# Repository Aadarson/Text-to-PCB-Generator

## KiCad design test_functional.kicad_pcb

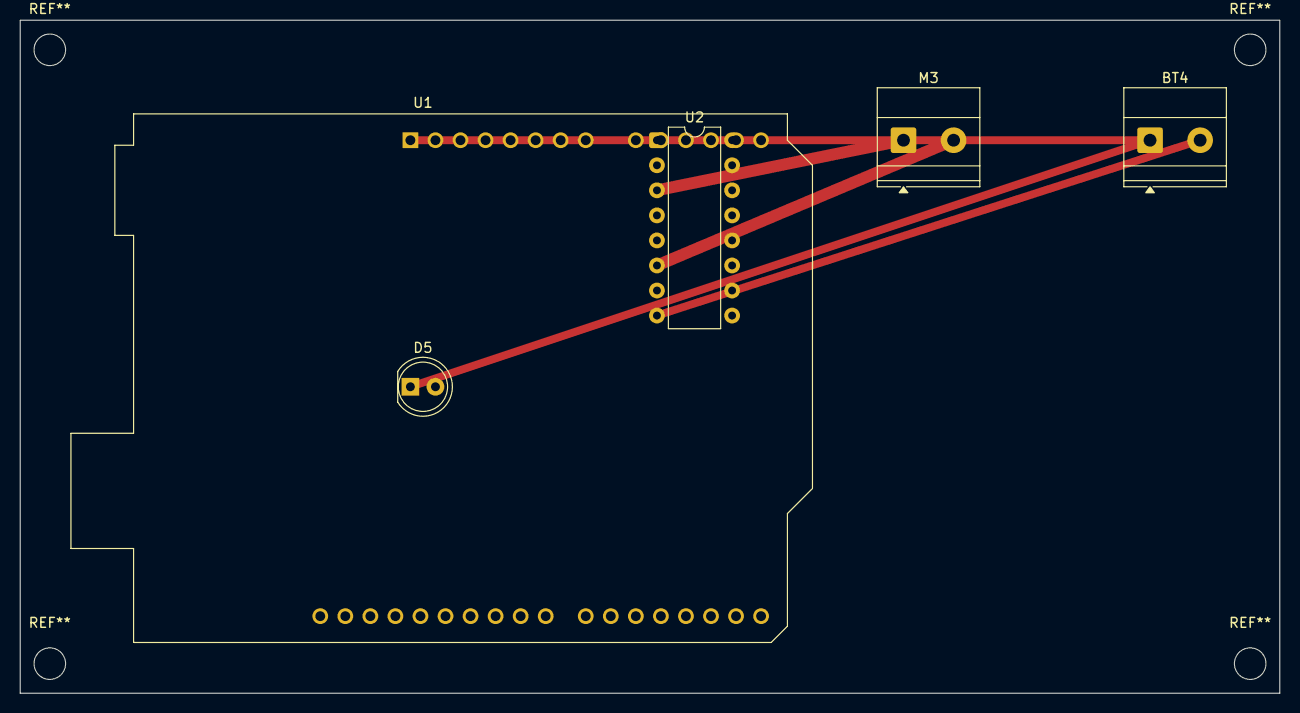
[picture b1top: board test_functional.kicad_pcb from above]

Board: 2 copper layers, 127.7 x 68.2 mm, 5 parts (0 on the bottom side), 4 nets.

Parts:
BT4: Battery; TerminalBlock_Phoenix_MKDS-1,5-2-5.08_1x02_P5.08mm_Horizont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
D5: LED; LED_D5.0mm
M3: Motor; TerminalBlock_Phoenix_MKDS-1,5-2-5.08_1x02_P5.08mm_Horizont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
U1: Arduino; Arduino_UNO_R3
U2: L293D; DIP-16_W7.62mm

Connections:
GND: BT4.1, D5.1, U1.1, U2.1
unnamed: BT4.2, U2.8
unnamed: M3.1, U2.3
unnamed: M3.2, U2.6

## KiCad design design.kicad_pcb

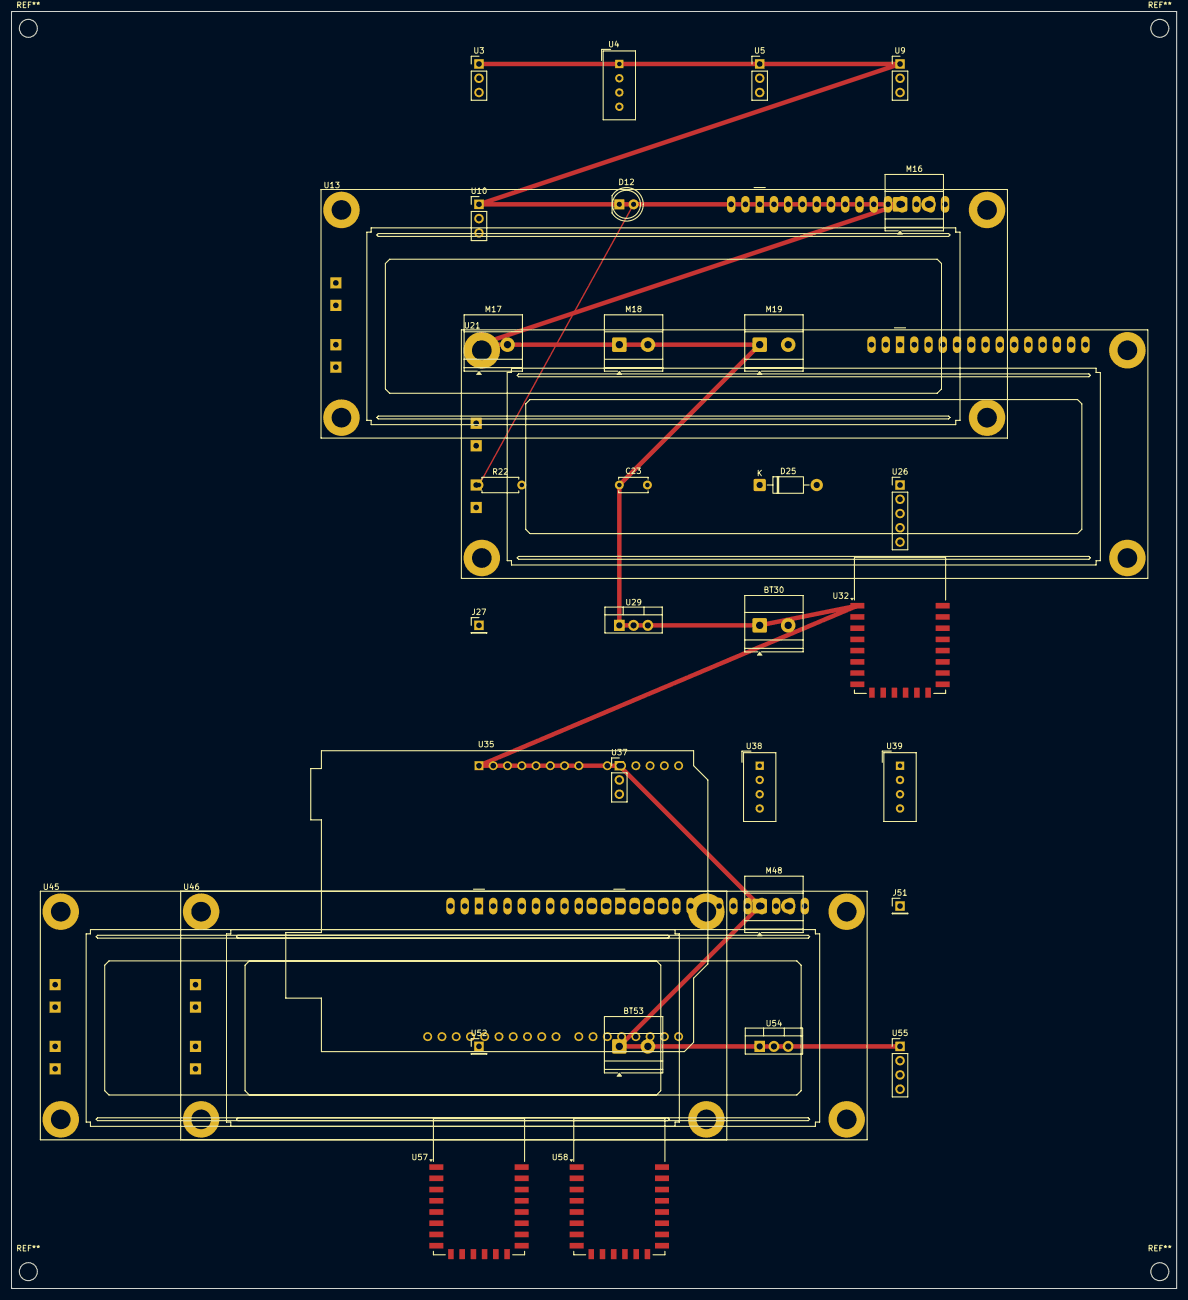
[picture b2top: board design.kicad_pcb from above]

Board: 2 copper layers, 207.6 x 227.5 mm, 34 parts (0 on the bottom side), 2 nets.

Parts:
BT30: Battery holders; TerminalBlock_Phoenix_MKDS-1,5-2-5.08_1x02_P5.08mm_Horizont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
BT53: battery; TerminalBlock_Phoenix_MKDS-1,5-2-5.08_1x02_P5.08mm_Horizont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
C23: Capacitors; C_Disc_D5.0mm_W2.5mm_P5.00mm
D12: LEDs; LED_D5.0mm
D25: Diodes; D_DO-41_SOD81_P10.16mm_Horizontal
J27: Jumper Wires; PinHeader_1x01_P2.54mm_Vertical
J51: Jumper; PinHeader_1x01_P2.54mm_Vertical
M16: Motors:; TerminalBlock_Phoenix_MKDS-1,5-2-5.08_1x02_P5.08mm_Horizont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
M17: DC motors; TerminalBlock_Phoenix_MKDS-1,5-2-5.08_1x02_P5.08mm_Horizont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
M18: Servo motors; TerminalBlock_Phoenix_MKDS-1,5-2-5.08_1x02_P5.08mm_Horizont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
M19: Stepper motors; TerminalBlock_Phoenix_MKDS-1,5-2-5.08_1x02_P5.08mm_Horizont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
M48: Motors; TerminalBlock_Phoenix_MKDS-1,5-2-5.08_1x02_P5.08mm_Horizont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
R22: Resistors; R_Axial_DIN0207_L6.3mm_D2.5mm_P7.62mm_Horizontal
U3: Sensors:; PinHeader_1x03_P2.54mm_Vertical
U4: Temperature sensors (DHT11, DHT22, LM35); Aosong_DHT11_5.5x12.0_P2.54mm
U5: Ultrasonic sensors (HC; PinHeader_1x03_P2.54mm_Vertical
U9: Sound sensors; PinHeader_1x03_P2.54mm_Vertical
U10: Touch sensors; PinHeader_1x03_P2.54mm_Vertical
U13: LCD Displays; LCD-016N002L
U21: Display; LCD-016N002L
U26: Breadboard; PinHeader_1x05_P2.54mm_Vertical
U29: Voltage regulators; TO-220-3_Vertical
U32: WiFi modules (ESP8266); ESP-12E
U35: arduino; Arduino_UNO_R3
U37: Sensors; PinHeader_1x03_P2.54mm_Vertical
U38: DHT11; Aosong_DHT11_5.5x12.0_P2.54mm
U39: DHT22; Aosong_DHT11_5.5x12.0_P2.54mm
U45: LCD; LCD-016N002L
U46: Displays; LCD-016N002L
U52: Wires; PinHeader_1x01_P2.54mm_Vertical
U54: regulators; TO-220-3_Vertical
U55: Modules; PinHeader_1x04_P2.54mm_Vertical
U57: WiFi; ESP-12E
U58: ESP8266; ESP-12E

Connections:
GND: BT30.1, BT53.1, C23.1, D12.1, M16.1, M17.1, M18.1, M19.1, M48.1, U3.1, U4.1, U5.1, U9.1, U10.1, U29.1, U32.1, U35.1, U37.1, U54.1, U55.1
unnamed: D12.2, R22.1

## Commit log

2026-02-17 Fix spaCy model install
2026-02-17 Fix pip externally managed environment
2026-02-17 Fix spaCy model install correctly
2026-02-17 Fix kicad-cli path for cloud deployment
